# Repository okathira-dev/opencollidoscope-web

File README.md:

# Open Collidoscope Web App

A browser-based port of [Open Collidoscope](https://code.soundsoftware.ac.uk/projects/opencollidoscope) — an interactive granular synthesizer where you record sound, explore it visually, and play it like a musical instrument.

**Live demo:** <https://okathira-dev.github.io/opencollidoscope-web/>

This web application's author is not the author of Open Collidoscope.

## What is Collidoscope?

Official site: <http://collidoscope.io/>

> Collidoscope is driven by our vision to make digital sound and music more palpable, immediate, and magical for both performers and audience.
> Collidoscope is an interactive musical instrument developed by [Ben Bengler](http://benbengler.com/) and [Fiore Martin](http://fioremartin.com/) in March 2015. Fill it with sound and explore, and in the next moment, play and perform it like a musical instrument.

## Features

- **Granular synthesis** — record audio and play it back as grains with real-time control
- **Waveform display** — chunk-based visualization with selection, playback cursor, and filter-linked alpha
- **Piano keyboard** — mouse, PC keyboard, and Web MIDI input
- **Hardware layouts** — original and new Collidoscope UI variants (`original` / `new`), with facing, stacked, and solo player layouts
- **Loop & filter** — loop toggle/push button and cutoff filter wired to the audio graph
- **Oscilloscope** — real-time output waveform display
- **Presets** — save/load configuration as JSON
- **Mic input settings** — gain, browser processing, compressor, and post-recording normalization (Web-only extension)
- **Fullscreen** — performance-friendly full-screen mode

## Usage

1. Open the [live demo](https://okathira-dev.github.io/opencollidoscope-web/) in a modern browser (Chrome, Edge, or Firefox recommended).
2. Click **音声を開始** to initialize audio (microphone permission is required for recording).
3. Record sound, select a region on the waveform, and play with the on-screen keyboard or a connected MIDI controller.

## Development

Prerequisites: **Node.js** `^24.14.0`, **pnpm** 11 (see `packageManager` in `package.json`).

```bash
pnpm install
pnpm dev          # dev server (Vite root is src/)
pnpm check        # Biome + tsc + markdownlint
pnpm test         # Vitest
pnpm build
```

Intentional trade-offs and gaps not yet implemented are documented in [docs/web-spec.md](docs/web-spec.md) under **開発環境の意図的な選択と未整備**.

## About this repository

This repository contains:

- **`src/`** — the web application (React, TypeScript, Web Audio API, AudioWorklet)
- **`opencollidoscope/`** — a clone of the [original Open Collidoscope source](https://code.soundsoftware.ac.uk/projects/opencollidoscope) (C++/Cinder), included for reference during porting
- **`opencollidoscope_downloads/`** — a PDF mirror of the official project's **Downloads** section (build guides, MIDI reference, CAD drawing PDFs). Binaries and 3D CAD sources are excluded via `.gitignore`; see [opencollidoscope_downloads/README.md](opencollidoscope_downloads/README.md)

The original source revision referenced during development is [18:f1ff1a81be20](https://code.soundsoftware.ac.uk/projects/opencollidoscope/repository/revisions/f1ff1a81be20d31608a4002546722d839f64b31e).

## Original project

| Resource | URL |
| --- | --- |
| Official site | <http://collidoscope.io/> |
| Open Collidoscope (source & binaries) | <https://code.soundsoftware.ac.uk/projects/opencollidoscope> |
| Official Downloads | <https://code.soundsoftware.ac.uk/projects/opencollidoscope/files> |

## License

### This web application

This web application is licensed under the **GNU General Public License v3.0 or later (GPL-3.0-or-later)**, matching the original Open Collidoscope software license. See [LICENSE](LICENSE).

### Original Open Collidoscope

The original Open Collidoscope software (CollidoscopeApp, CollidoscopeTeensy, and distributed binaries) is:

- **License:** GNU General Public License v3.0 (GPL-3.0)
- **Copyright:** Queen Mary University of London
- **Authors:** Ben Bengler, Fiore Martin

Source headers and the full license text are in [`opencollidoscope/GPLv3_license.txt`](opencollidoscope/GPLv3_license.txt).

### Official Downloads (mirrored materials)

Materials in [`opencollidoscope_downloads/`](opencollidoscope_downloads/) were published separately from the source code in the official project's **Downloads** section. Their licenses differ by component:

| Component | License |
| --- | --- |
| Software source & binaries | GPL-3.0 |
| PCB designs | [CC BY-SA 3.0](https://creativecommons.org/licenses/by-sa/3.0/) (Ben Bengler) |
| 3D CAD files & build instructions | CC BY-SA 3.0 |

See [`opencollidoscope_downloads/CAD/license.txt`](opencollidoscope_downloads/CAD/license.txt) for the CAD license text.

## Documentation

| Document | Description |
| --- | --- |
| [docs/README.md](docs/README.md) | Documentation index — what to write where (single source of truth) |
| [docs/original-analysis.md](docs/original-analysis.md) | Analysis of the original C++ implementation |
| [docs/ui-mapping.md](docs/ui-mapping.md) | Electronic mapping, physical controls, Web UI gap analysis |
| [docs/web-spec.md](docs/web-spec.md) | Web version goals, features, and configuration |
| [docs/web-design.md](docs/web-design.md) | Web version architecture and porting design |

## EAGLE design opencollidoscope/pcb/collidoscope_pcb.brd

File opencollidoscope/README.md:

# Open Collidoscope

**This file does not exist in the original repository.**
**This repository's owner is not the author of Open Collidoscope.**

This repository is a clone of the [Open Collidoscope project](https://code.soundsoftware.ac.uk/projects/opencollidoscope), which is publicly released under the GPLv3 license.

## What is Collidoscope?

official site <http://collidoscope.io/>

> Collidoscope is driven by our vision to make digital sound and music more palpable, immediate, and magical for both performers and audience.
> Collidoscope is an interactive musical instrument developed by [Ben Bengler](http://benbengler.com/) and [Fiore Martin](http://fioremartin.com/) in March 2015. Fill it with sound and explore, and in the next moment, play and perform it like a musical instrument.

- official repository: <https://code.soundsoftware.ac.uk/projects/opencollidoscope>
- revision: [18:f1ff1a81be20](https://code.soundsoftware.ac.uk/projects/opencollidoscope/repository/revisions/f1ff1a81be20d31608a4002546722d839f64b31e)

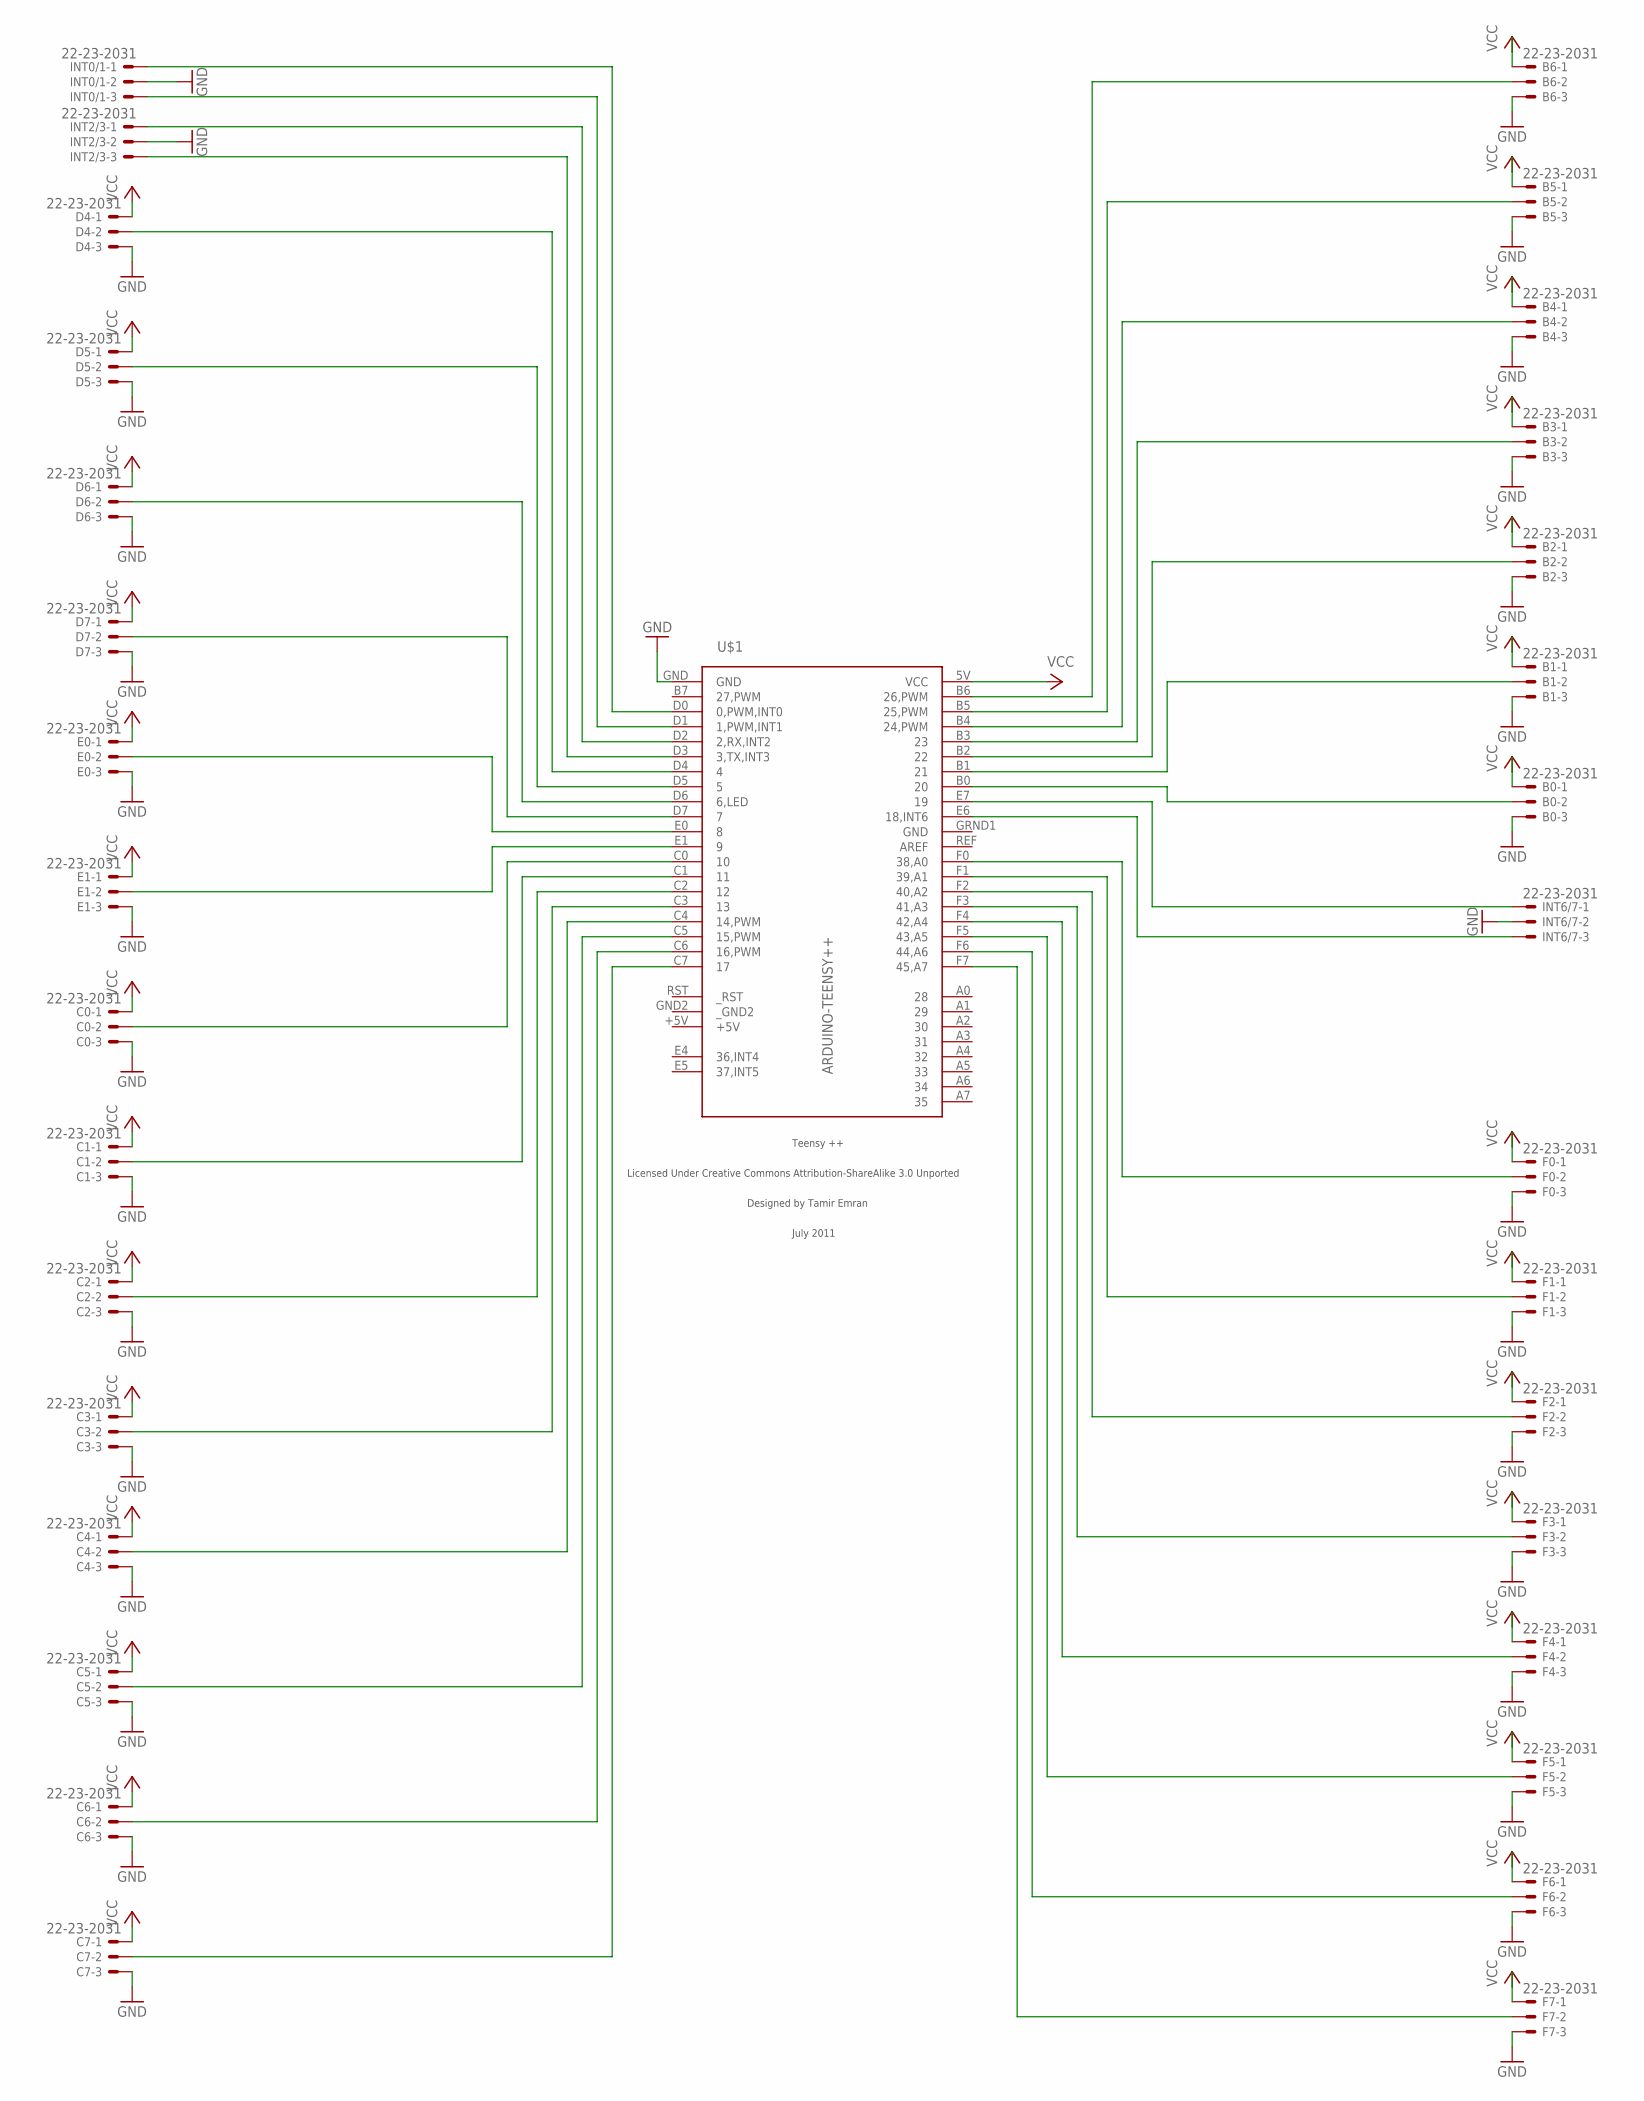
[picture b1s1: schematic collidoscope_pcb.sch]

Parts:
B0, B1, B2, B3, B4, B5, B6: 22-23-2031
C0, C1, C2, C3, C4, C5, C6, C7: 22-23-2031
D4, D5, D6, D7: 22-23-2031
E0, E1: 22-23-2031
F0, F1, F2, F3, F4, F5, F6, F7: 22-23-2031
INT0/1, INT2/3, INT6/7: 22-23-2031
U$1: ARDUINO-TEENSY++; TEENSY++

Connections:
+5V: U$1.+5V
GND: B0.3, B1.3, B2.3, B3.3, B4.3, B5.3, B6.3, C0.3, C1.3, C2.3, C3.3, C4.3, C5.3, C6.3, C7.3, D4.3, D5.3, D6.3, D7.3, E0.3, E1.3, F0.3, F1.3, F2.3, F3.3, F4.3, F5.3, F6.3, F7.3, INT0/1.2, INT2/3.2, INT6/7.2, U$1.GND, U$1.GRND1 (GND)
unnamed: B6.2, U$1.B6 (26,PWM)
unnamed: B5.2, U$1.B5 (25,PWM)
unnamed: B4.2, U$1.B4 (24,PWM)
unnamed: B3.2, U$1.B3 (23)
unnamed: B2.2, U$1.B2 (22)
unnamed: B1.2, U$1.B1 (21)
unnamed: B0.2, U$1.B0 (20)
unnamed: INT6/7.1, U$1.E7 (19)
unnamed: INT6/7.3, U$1.E6 (18,INT6)
unnamed: F0.2, U$1.F0 (38,A0)
unnamed: F1.2, U$1.F1 (39,A1)
unnamed: F2.2, U$1.F2 (40,A2)
unnamed: F3.2, U$1.F3 (41,A3)
unnamed: F4.2, U$1.F4 (42,A4)
unnamed: F5.2, U$1.F5 (43,A5)
unnamed: F6.2, U$1.F6 (44,A6)
unnamed: F7.2, U$1.F7 (45,A7)
unnamed: INT0/1.1, U$1.D0 (0,PWM,INT0)
unnamed: INT0/1.3, U$1.D1 (1,PWM,INT1)
unnamed: INT2/3.1, U$1.D2 (2,RX,INT2)
unnamed: INT2/3.3, U$1.D3 (3,TX,INT3)
unnamed: D4.2, U$1.D4 (4)
unnamed: D5.2, U$1.D5 (5)
unnamed: D6.2, U$1.D6 (6,LED)
unnamed: D7.2, U$1.D7 (7)
unnamed: E0.2, U$1.E0 (8)
unnamed: E1.2, U$1.E1 (9)
unnamed: C0.2, U$1.C0 (10)
unnamed: C1.2, U$1.C1 (11)
unnamed: C2.2, U$1.C2 (12)
unnamed: C3.2, U$1.C3 (13)
unnamed: C4.2, U$1.C4 (14,PWM)
unnamed: C5.2, U$1.C5 (15,PWM)
unnamed: C6.2, U$1.C6 (16,PWM)
unnamed: C7.2, U$1.C7 (17)
VCC: B0.1, B1.1, B2.1, B3.1, B4.1, B5.1, B6.1, C0.1, C1.1, C2.1, C3.1, C4.1, C5.1, C6.1, C7.1, D4.1, D5.1, D6.1, D7.1, E0.1, E1.1, F0.1, F1.1, F2.1, F3.1, F4.1, F5.1, F6.1, F7.1, U$1.5V (VCC)
_GND2: U$1.GND2 (_GND2)

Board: 2 copper layers, 33 parts (0 on the bottom side), 37 nets, no tracks yet.

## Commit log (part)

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2025-04-18 clone
2025-04-19 feat: reactプロジェクトのセットアップ
2025-04-19 build(deps-dev): bump eslint-import-resolver-typescript
    Bumps [eslint-import-resolver-typescript](https://github.com/import-js/eslint-import-resolver-typescript) from 3.10.0 to 4.3.2.
    - [Release notes](https://github.com/import-js/eslint-import-resolver-typescript/releases)
    - [Changelog](https://github.com/import-js/eslint-import-resolver-typescript/blob/master/CHANGELOG.md)
    - [Commits](https://github.com/import-js/eslint-import-resolver-typescript/compare/v3.10.0...v4.3.2)
    ---
    updated-dependencies:
2025-04-19 build(deps): bump react and @types/react
    Bumps [react](https://github.com/facebook/react/tree/HEAD/packages/react) and [@types/react](https://github.com/DefinitelyTyped/DefinitelyTyped/tree/HEAD/types/react). These dependencies needed to be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
    Updates `react` from 18.3.1 to 19.1.0
    - [Release notes](https://github.com/facebook/react/releases)
    - [Changelog](https://github.com/facebook/react/blob/main/CHANGELOG.md)
    - [Commits](https://github.com/facebook/react/commits/v19.1.0/packages/react)
    Updates `@types/react` from 18.3.20 to 19.1.2
2025-04-19 build(deps): bump @mui/material from 6.4.11 to 7.0.2
    Bumps [@mui/material](https://github.com/mui/material-ui/tree/HEAD/packages/mui-material) from 6.4.11 to 7.0.2.
    - [Release notes](https://github.com/mui/material-ui/releases)
    - [Changelog](https://github.com/mui/material-ui/blob/master/CHANGELOG.md)
    - [Commits](https://github.com/mui/material-ui/commits/v7.0.2/packages/mui-material)
    ---
    updated-dependencies:
2025-04-19 build(deps): bump react-dom and @types/react-dom
    Bumps [react-dom](https://github.com/facebook/react/tree/HEAD/packages/react-dom) and [@types/react-dom](https://github.com/DefinitelyTyped/DefinitelyTyped/tree/HEAD/types/react-dom). These dependenc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
    Updates `react-dom` from 18.3.1 to 19.1.0
    - [Release notes](https://github.com/facebook/react/releases)
    - [Changelog](https://github.com/facebook/react/blob/main/CHANGELOG.md)
    - [Commits](https://github.com/facebook/react/commits/v19.1.0/packages/react-dom)
    Updates `@types/react-dom` from 18.3.6 to 19.1.2
2025-04-19 build(deps): bump @mui/icons-material from 6.4.11 to 7.0.2
    Bumps [@mui/icons-material](https://github.com/mui/material-ui/tree/HEAD/packages/mui-icons-material) from 6.4.11 to 7.0.2.
    - [Release notes](https://github.com/mui/material-ui/releases)
    - [Changelog](https://github.com/mui/material-ui/blob/master/CHANGELOG.md)
    - [Commits](https://github.com/mui/material-ui/commits/v7.0.2/packages/mui-icons-material)
    ---
    updated-dependencies:
2025-04-19 chore: Update README.md
2025-04-21 chore(deps-dev): bump eslint-import-resolver-typescript
    Bumps [eslint-import-resolver-typescript](https://github.com/import-js/eslint-import-resolver-typescript) from 3.10.0 to 4.3.4.
    - [Release notes](https://github.com/import-js/eslint-import-resolver-typescript/releases)
    - [Changelog](https://github.com/import-js/eslint-import-resolver-typescript/blob/master/CHANGELOG.md)
    - [Commits](https://github.com/import-js/eslint-import-resolver-typescript/compare/v3.10.0...v4.3.4)
    ---
    updated-dependencies:
2025-05-12 chore(deps): bump @mui/material from 6.4.11 to 7.1.0
    Bumps [@mui/material](https://github.com/mui/material-ui/tree/HEAD/packages/mui-material) from 6.4.11 to 7.1.0.
    - [Release notes](https://github.com/mui/material-ui/releases)
    - [Changelog](https://github.com/mui/material-ui/blob/master/CHANGELOG.md)
    - [Commits](https://github.com/mui/material-ui/commits/v7.1.0/packages/mui-material)
    ---
    updated-dependencies:
2025-05-19 chore(deps-dev): bump eslint-import-resolver-typescript
    Bumps [eslint-import-resolver-typescript](https://github.com/import-js/eslint-import-resolver-typescript) from 3.10.0 to 4.3.5.
    - [Release notes](https://github.com/import-js/eslint-import-resolver-typescript/releases)
    - [Changelog](https://github.com/import-js/eslint-import-resolver-typescript/blob/master/CHANGELOG.md)
    - [Commits](https://github.com/import-js/eslint-import-resolver-typescript/compare/v3.10.0...v4.3.5)
    ---
    updated-dependencies:
2025-05-26 chore(deps-dev): bump eslint-import-resolver-typescript
    Bumps [eslint-import-resolver-typescript](https://github.com/import-js/eslint-import-resolver-typescript) from 3.10.0 to 4.4.1.
    - [Release notes](https://github.com/import-js/eslint-import-resolver-typescript/releases)
    - [Changelog](https://github.com/import-js/eslint-import-resolver-typescript/blob/master/CHANGELOG.md)
    - [Commits](https://github.com/import-js/eslint-import-resolver-typescript/compare/v3.10.0...v4.4.1)
    ---
    updated-dependencies:
2025-06-02 chore(deps): bump @mui/icons-material from 6.4.11 to 7.1.1
    Bumps [@mui/icons-material](https://github.com/mui/material-ui/tree/HEAD/packages/mui-icons-material) from 6.4.11 to 7.1.1.
    - [Release notes](https://github.com/mui/material-ui/releases)
    - [Changelog](https://github.com/mui/material-ui/blob/master/CHANGELOG.md)
    - [Commits](https://github.com/mui/material-ui/commits/v7.1.1/packages/mui-icons-material)
    ---
    updated-dependencies:
2025-06-02 chore(deps-dev): bump eslint-import-resolver-typescript
    Bumps [eslint-import-resolver-typescript](https://github.com/import-js/eslint-import-resolver-typescript) from 3.10.0 to 4.4.2.
    - [Release notes](https://github.com/import-js/eslint-import-resolver-typescript/releases)
    - [Changelog](https://github.com/import-js/eslint-import-resolver-typescript/blob/master/CHANGELOG.md)
    - [Commits](https://github.com/import-js/eslint-import-resolver-typescript/compare/v3.10.0...v4.4.2)
    ---
    updated-dependencies:
2025-06-02 chore(deps): bump @mui/material from 6.4.11 to 7.1.1
    Bumps [@mui/material](https://github.com/mui/material-ui/tree/HEAD/packages/mui-material) from 6.4.11 to 7.1.1.
    - [Release notes](https://github.com/mui/material-ui/releases)
    - [Changelog](https://github.com/mui/material-ui/blob/master/CHANGELOG.md)
    - [Commits](https://github.com/mui/material-ui/commits/v7.1.1/packages/mui-material)
    ---
    updated-dependencies:
2025-06-09 chore(deps-dev): bump eslint-import-resolver-typescript
    Bumps [eslint-import-resolver-typescript](https://github.com/import-js/eslint-import-resolver-typescript) from 3.10.0 to 4.4.3.
    - [Release notes](https://github.com/import-js/eslint-import-resolver-typescript/releases)
    - [Changelog](https://github.com/import-js/eslint-import-resolver-typescript/blob/master/CHANGELOG.md)
    - [Commits](https://github.com/import-js/eslint-import-resolver-typescript/compare/v3.10.0...v4.4.3)
    ---
    updated-dependencies:
2025-06-23 chore(deps): bump @mui/icons-material from 6.4.11 to 7.1.2
    Bumps [@mui/icons-material](https://github.com/mui/material-ui/tree/HEAD/packages/mui-icons-material) from 6.4.11 to 7.1.2.
    - [Release notes](https://github.com/mui/material-ui/releases)
    - [Changelog](https://github.com/mui/material-ui/blob/v7.1.2/CHANGELOG.md)
    - [Commits](https://github.com/mui/material-ui/commits/v7.1.2/packages/mui-icons-material)
    ---
    updated-dependencies:
2025-06-30 chore(deps-dev): bump eslint-import-resolver-typescript
    Bumps [eslint-import-resolver-typescript](https://github.com/import-js/eslint-import-resolver-typescript) from 3.10.0 to 4.4.4.
    - [Release notes](https://github.com/import-js/eslint-import-resolver-typescript/releases)
    - [Changelog](https://github.com/import-js/eslint-import-resolver-typescript/blob/master/CHANGELOG.md)
    - [Commits](https://github.com/import-js/eslint-import-resolver-typescript/compare/v3.10.0...v4.4.4)
    ---
    updated-dependencies:
2025-07-03 Checkpoint before follow-up message
2025-07-03 Add sample loading and granular piano keyboard with Tone.js
2025-07-03 Improve grain synthesis pitch shifting with precise chromatic ratio calculation
2025-07-03 Add grain synth controls and waveform visualization
2025-07-03 Implement full OpenCollidoscope Web granular synthesizer with UI and audio
2025-07-03 Fix build errors, add debug console, and resolve module import issues
2025-07-03 Refactor imports, improve type safety, and optimize waveform rendering
2025-07-03 Refactor code formatting and remove trailing newline characters
2025-07-03 Optimize project structure, resolve ESLint errors, and improve TypeScript best practices
2025-07-05 feat: Web版実装の仕様を整理する
2025-07-05 feat: [WIP] ざっくりページの作成
2025-07-05 docs: 設計と仕様を固める
2025-07-05 docs: 設計書の明確化
2025-07-06 docs: 計画
2025-07-06 feat: 録音再生部分作成
2025-07-15 chore(deps): bump @mui/material from 6.4.11 to 7.2.0
    Bumps [@mui/material](https://github.com/mui/material-ui/tree/HEAD/packages/mui-material) from 6.4.11 to 7.2.0.
    - [Release notes](https://github.com/mui/material-ui/releases)
    - [Changelog](https://github.com/mui/material-ui/blob/master/CHANGELOG.md)
    - [Commits](https://github.com/mui/material-ui/commits/v7.2.0/packages/mui-material)
    ---
    updated-dependencies:
2025-07-15 chore(deps): bump @mui/icons-material from 6.4.11 to 7.2.0
    ---
    updated-dependencies:
    - dependency-name: "@mui/icons-material"
    dependency-version: 7.2.0
    dependency-type: direct:production
    update-type: version-update:semver-major
2025-08-12 chore(deps): bump @mui/material from 6.4.11 to 7.3.1
    Bumps [@mui/material](https://github.com/mui/material-ui/tree/HEAD/packages/mui-material) from 6.4.11 to 7.3.1.
    - [Release notes](https://github.com/mui/material-ui/releases)
    - [Changelog](https://github.com/mui/material-ui/blob/master/CHANGELOG.md)
    - [Commits](https://github.com/mui/material-ui/commits/v7.3.1/packages/mui-material)
    ---
    updated-dependencies:
2025-08-12 chore(deps): bump @mui/icons-material from 6.4.11 to 7.3.1
    Bumps [@mui/icons-material](https://github.com/mui/material-ui/tree/HEAD/packages/mui-icons-material) from 6.4.11 to 7.3.1.
    - [Release notes](https://github.com/mui/material-ui/releases)
    - [Changelog](https://github.com/mui/material-ui/blob/master/CHANGELOG.md)
    - [Commits](https://github.com/mui/material-ui/commits/v7.3.1/packages/mui-icons-material)
    ---
    updated-dependencies:
2025-09-08 chore(deps): bump @mui/material from 6.4.11 to 7.3.2
    Bumps [@mui/material](https://github.com/mui/material-ui/tree/HEAD/packages/mui-material) from 6.4.11 to 7.3.2.
    - [Release notes](https://github.com/mui/material-ui/releases)
    - [Changelog](https://github.com/mui/material-ui/blob/master/CHANGELOG.md)
    - [Commits](https://github.com/mui/material-ui/commits/v7.3.2/packages/mui-material)
    ---
    updated-dependencies:
2025-09-08 chore(deps): bump @mui/icons-material from 6.4.11 to 7.3.2
    Bumps [@mui/icons-material](https://github.com/mui/material-ui/tree/HEAD/packages/mui-icons-material) from 6.4.11 to 7.3.2.
    - [Release notes](https://github.com/mui/material-ui/releases)
    - [Changelog](https://github.com/mui/material-ui/blob/master/CHANGELOG.md)
    - [Commits](https://github.com/mui/material-ui/commits/v7.3.2/packages/mui-icons-material)
    ---
    updated-dependencies:
2025-10-06 chore(deps): bump @mui/icons-material from 6.4.11 to 7.3.4
    Bumps [@mui/icons-material](https://github.com/mui/material-ui/tree/HEAD/packages/mui-icons-material) from 6.4.11 to 7.3.4.
    - [Release notes](https://github.com/mui/material-ui/releases)
    - [Changelog](https://github.com/mui/material-ui/blob/master/CHANGELOG.md)
    - [Commits](https://github.com/mui/material-ui/commits/v7.3.4/packages/mui-icons-material)
    ---
    updated-dependencies:
2025-10-06 chore(deps): bump @mui/material from 6.4.11 to 7.3.4
    Bumps [@mui/material](https://github.com/mui/material-ui/tree/HEAD/packages/mui-material) from 6.4.11 to 7.3.4.
    - [Release notes](https://github.com/mui/material-ui/releases)
    - [Changelog](https://github.com/mui/material-ui/blob/master/CHANGELOG.md)
    - [Commits](https://github.com/mui/material-ui/commits/v7.3.4/packages/mui-material)
    ---
    updated-dependencies:
2026-06-20 feat: テスト、開発基盤整備
2026-06-20 docs: ドキュメント再構成
2026-06-21 docs: 計画調整
2026-06-21 docs: gitルール修正
2026-06-21 chore: workletの型に `@types` のものを当てる
2026-06-21 fix: dependabot修正
2026-06-21 feat: M1: 録音 → 波形表示
2026-06-21 feat: グラニュラーの基本を実装
2026-06-25 docs: ワイヤーフレーム作成の準備を整える

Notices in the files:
parts and their libraries:
teensypp: Licensed Under Creative Commons
teensypp: Licensed Under Creative Commons Attribution-ShareAlike 3.0 Unported
teensypp: Licensed Under Creative Commons Attribution-ShareAlike 3.0 Unported (CC BY-SA 3.0)
